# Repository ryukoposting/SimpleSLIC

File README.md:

SimpleSLIC is an expansion board for a KS0835 Subscriber Loop Interface Card.
This board makes it easy to serve a telephone line from any 3.3V or 5V
microcontroller.

# Basic Use

1. Connect the Vcc pin to 3.3 or 5 Volts.
2. Connect the GND pin to ground.
3. Hook up a telephone to the phone jack.
4. To make the phone ring, pull the RM pin up to Vcc, and toggle the FR pin at
   20 Hz.

# Warning

This device is *NOT* intended to connect to a telephone line. Rather, this
device *is a phone line.* You connect phones and modems to this board, not other
phone lines. Likewise, do not connect two copies of this board directly together
by their phone jacks.

If you want to connect two boards together via their phone lines, use a pair of
600:600 audio transformers attached to the tip/ring pins of each board.

# Licensing

This project is licensed under the terms of CERN-OHL-S, Version 2. A copy of the
license can be found in the `LICENSE` file included in this repository.

This repository contains files from third-party sources. Such files are located
in the `Libraries/3rdparty` directory. Licensing information for these files has
been included with those files, when such information was provided by the
vendor.

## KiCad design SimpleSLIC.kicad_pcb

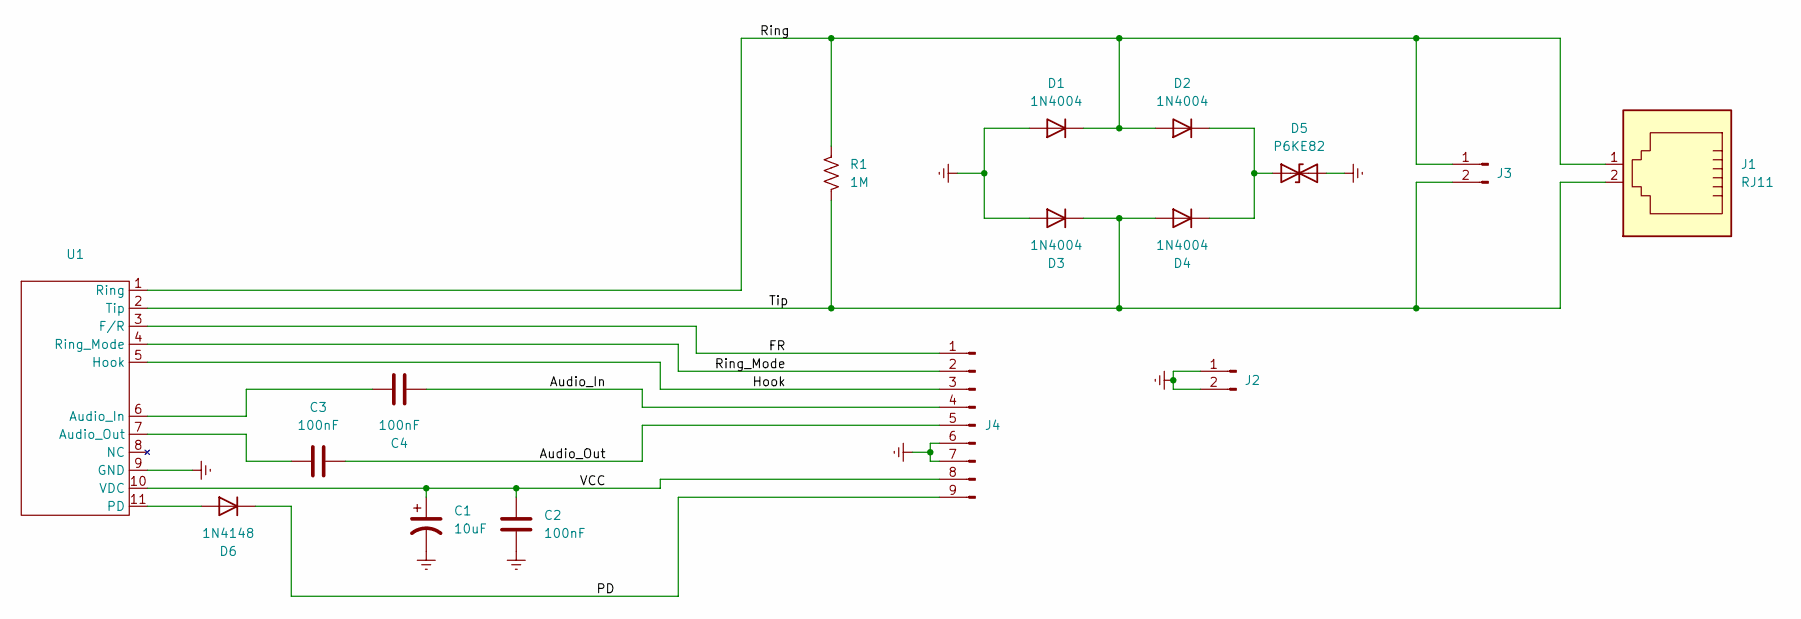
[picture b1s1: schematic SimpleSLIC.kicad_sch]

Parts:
C1: 10uF; CP_Radial_D5.0mm_P2.50mm
C2, C3, C4: 100nF; C_Disc_D4.7mm_W2.5mm_P5.00mm
D1, D2, D3, D4: 1N4004; D_DO-41_SOD81_P10.16mm_Horizontal
D5: P6KE82; D_DO-15_P12.70mm_Horizontal
D6: 1N4148; D_DO-35_SOD27_P7.62mm_Horizontal
J1: RJ11; RJ11_438600003
J2, J3: Conn_01x02_Pin; PinHeader_1x02_P2.54mm_Vertical
J4: Conn_01x09_Pin; PinHeader_1x09_P2.54mm_Vertical
R1: 1M; R_Axial_DIN0207_L6.3mm_D2.5mm_P10.16mm_Horizontal
U1: KS0835F

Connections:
/Audio_In: C4.2, J4.4
/Audio_Out: C3.2, J4.5
/FR: J4.1, U1.3 (F/R)
/Hook: J4.3, U1.5 (Hook)
/PD: D6.1 (K), J4.9
/Ring: D1.1 (K), D2.2 (A), J1.1, J3.1, R1.1, U1.1 (Ring)
/Ring_Mode: J4.2, U1.4 (Ring_Mode)
/Tip: D3.1 (K), D4.2 (A), J1.2, J3.2, R1.2, U1.2 (Tip)
/VCC: C1.1, C2.1, J4.8, U1.10 (VDC)
GNDREF: C1.2, C2.2, D1.2 (A), D3.2 (A), D5.2 (A2), J2.1, J2.2, J4.6, J4.7, U1.9 (GND)
unnamed: D2.1 (K), D4.1 (K), D5.1 (A1)
unnamed: D6.2 (A), U1.11 (PD)
unnamed: C4.1, U1.6 (Audio_In)
unnamed: C3.1, U1.7 (Audio_Out)

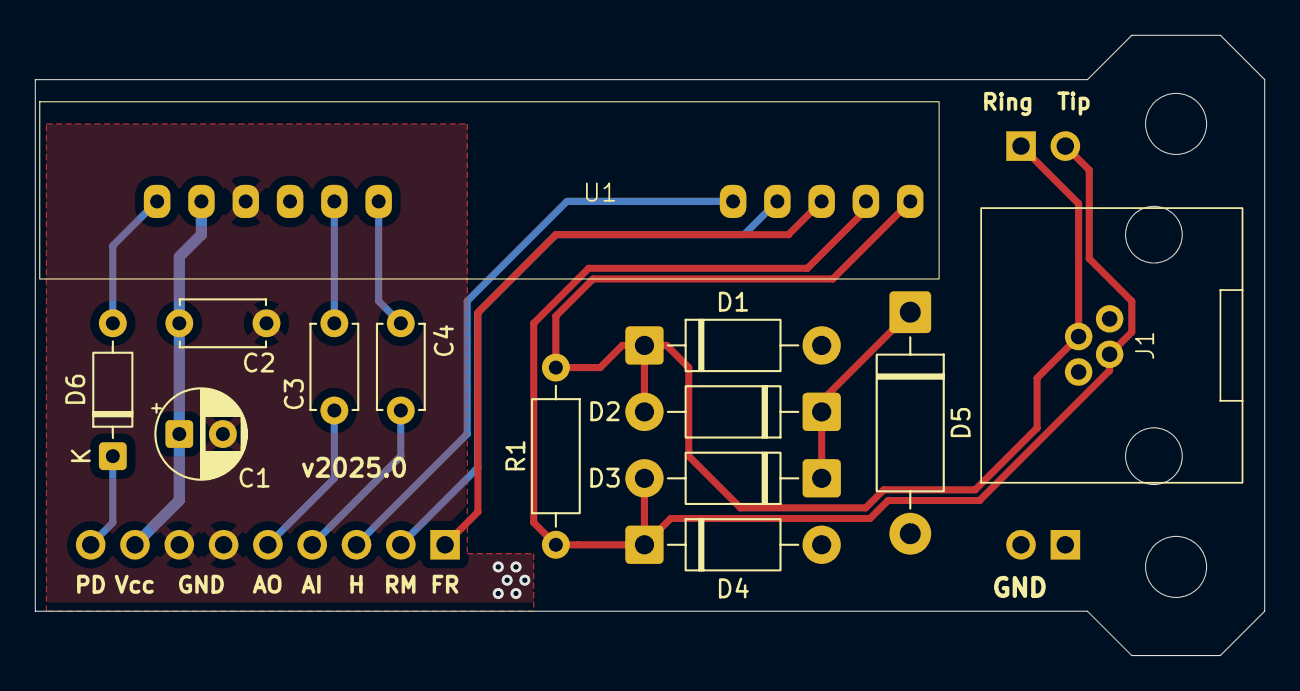
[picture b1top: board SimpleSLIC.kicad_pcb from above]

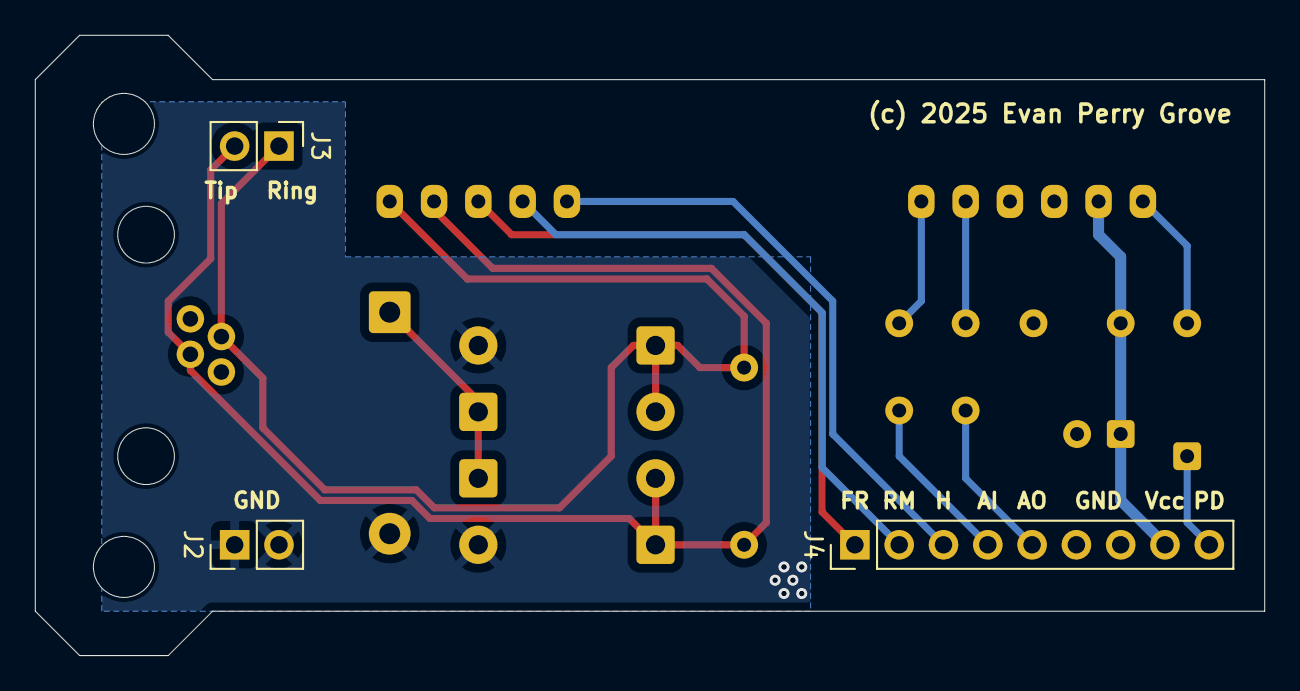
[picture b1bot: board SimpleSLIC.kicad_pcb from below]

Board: 2 copper layers, 70.5 x 35.6 mm, 16 parts (3 on the bottom side), 14 nets.

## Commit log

2025-08-12 Update BOM

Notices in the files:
SimpleSLIC.kicad_pcb:
(c) 2025 Evan Perry Grove
